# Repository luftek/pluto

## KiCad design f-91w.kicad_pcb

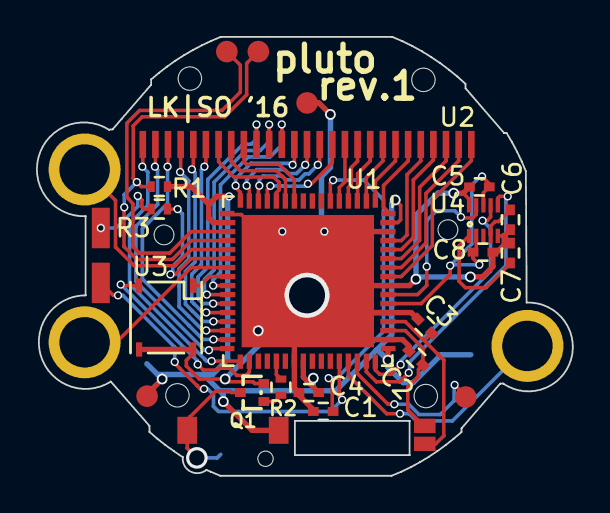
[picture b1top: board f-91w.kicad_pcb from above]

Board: 2 copper layers, 29.8 x 24.4 mm, 37 parts (0 on the bottom side), 52 nets.

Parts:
C1: 4.7u; C_0402
C2, C3: 22p; C_0402
C4, C5, C6, C7, C8: 100n; C_0402
MH1, MH2, MH3, MH4, MH5, MH6, MH7: 1pin
P1, P2, P3, P4, P5, P6, P7, P8, P9, P10, P11, P13, P14, P15: CONN_01X01; 1pin
Q1: BC846; SOT416
R1, R3: 10k; R_0402
R2: 47k; R_0402
U1: MSP430FR6972; QFN-64-1EP_9x9mm_Pitch0.5mm
U2: LCD-F-91W
U3: TSOP57xxx
U4: MAG3110; DFN-10-1EP_2x2mm_Pitch0.4mm

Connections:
/BUZ: P9.1, Q1.3
/B_ALARM: P7.1, U1.45
/B_LIGHT: P5.1, U1.21
/B_MODE: P6.1, U1.23
/INT1: U1.55, U4.9
/IR: U1.24, U3.1
/IR_PWR: U1.34, U3.5
/LCD_COM1: U1.12, U2.7
/LCD_COM2: U1.11, U2.8
/LCD_COM3: U1.10, U2.9
/LCD_SEG1: U1.33, U2.1
/LCD_SEG2: U1.32, U2.2
/LCD_SEG3: U1.31, U2.3
/LCD_SEG4: U1.30, U2.4
/LCD_SEG5: U1.29, U2.5
/LCD_SEG6: U1.28, U2.6
/LCD_SEG7: U1.27, U2.10
/LCD_SEG8: U1.26, U2.11
/LCD_SEG9: U1.25, U2.12
/LCD_SEG10: U1.16, U2.13
/LCD_SEG11: U1.15, U2.14
/LCD_SEG12: U1.14, U2.15
/LCD_SEG13: U1.13, U2.16
/LCD_SEG14: U1.5, U2.17
/LCD_SEG15: U1.4, U2.18
/LCD_SEG16: U1.3, U2.19
/LCD_SEG17: U1.2, U2.20
/LCD_SEG18: U1.1, U2.21
/LCD_SEG19: U1.64, U2.22
/LCD_SEG20: U1.61, U2.23
/LCD_SEG21: U1.60, U2.24
/LCD_SEG22: U1.59, U2.25
/LCD_SEG23: U1.58, U2.26
/LCD_SEG24: U1.57, U2.27
/LED_1: P11.1, U1.44
/LED_2: R3.2, U1.22
/MAG_PWR: C5.2, C8.1, U1.54, U4.2, U4.8
/Q-1: C2.1, P1.1, U1.51
/Q-2: C3.1, P2.1, U1.52
/SCL: U1.48, U4.7
/SDA: U1.47, U4.6
GND: C1.2, C2.2, C3.2, C4.2, C5.1, C6.2, C7.2, C8.2, P13.1, Q1.2, U1.17, U1.39, U1.50, U1.53, U1.56, U1.62, U1.65, U3.6, U4.5, U4.10
unnamed: C1.1, U1.6
unnamed: C6.1, U4.4
unnamed: C7.1, U4.1
unnamed: P3.1, U1.19
unnamed: P4.1, R1.2, U1.20
unnamed: P10.1, R3.1
unnamed: P15.1, U1.46
unnamed: Q1.1, R2.2
unnamed: R2.1, U1.37
VCC: C4.1, P8.1, P14.1, R1.1, U1.18, U1.40, U1.49, U1.63

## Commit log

2017-12-29 OUTLINE: Change only Edge.Cuts layer to include "ears". Manufactiring process "castellated holes" is not necessary -> should reduce cost of production
